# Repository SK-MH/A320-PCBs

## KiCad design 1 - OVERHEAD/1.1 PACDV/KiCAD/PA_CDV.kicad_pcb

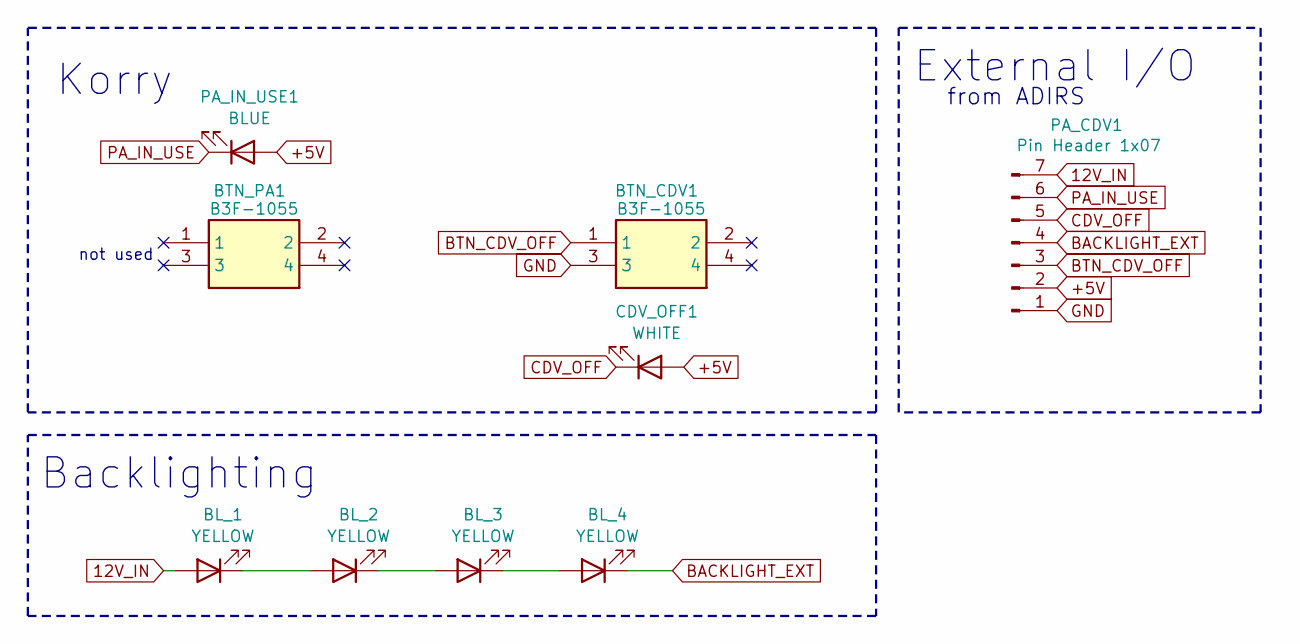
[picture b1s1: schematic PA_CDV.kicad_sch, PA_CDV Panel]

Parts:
BL_1, BL_2, BL_3, BL_4: YELLOW; LED_D3.0mm
BTN_CDV1: B3F-1055; B3F1000; Mouser Part Number 653-B3F-1055
BTN_PA1: B3F-1055; B3F1000; Mouser Part Number 653-B3F-1055
CDV_OFF1: WHITE; LED_D3.0mm
PA_CDV1: Pin Header 1x07; JST_EH_B7B-EH-A_1x07_P2.50mm_Vertical
PA_IN_USE1: BLUE; LED_D3.0mm

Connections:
12V_IN: BL_1.2 (A), PA_CDV1.7
+5V: CDV_OFF1.2 (A), PA_CDV1.2, PA_IN_USE1.2 (A)
BACKLIGHT_EXT: BL_4.1 (K), PA_CDV1.4
BTN_CDV_OFF: BTN_CDV1.1, PA_CDV1.3
CDV_OFF: CDV_OFF1.1 (K), PA_CDV1.5
GND: BTN_CDV1.3, PA_CDV1.1
unnamed: BL_1.1 (K), BL_2.2 (A)
unnamed: BL_2.1 (K), BL_3.2 (A)
unnamed: BL_3.1 (K), BL_4.2 (A)
PA_IN_USE: PA_CDV1.6, PA_IN_USE1.1 (K)

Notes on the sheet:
External I/O
from ADIRS
Backlighting
Korry
not used

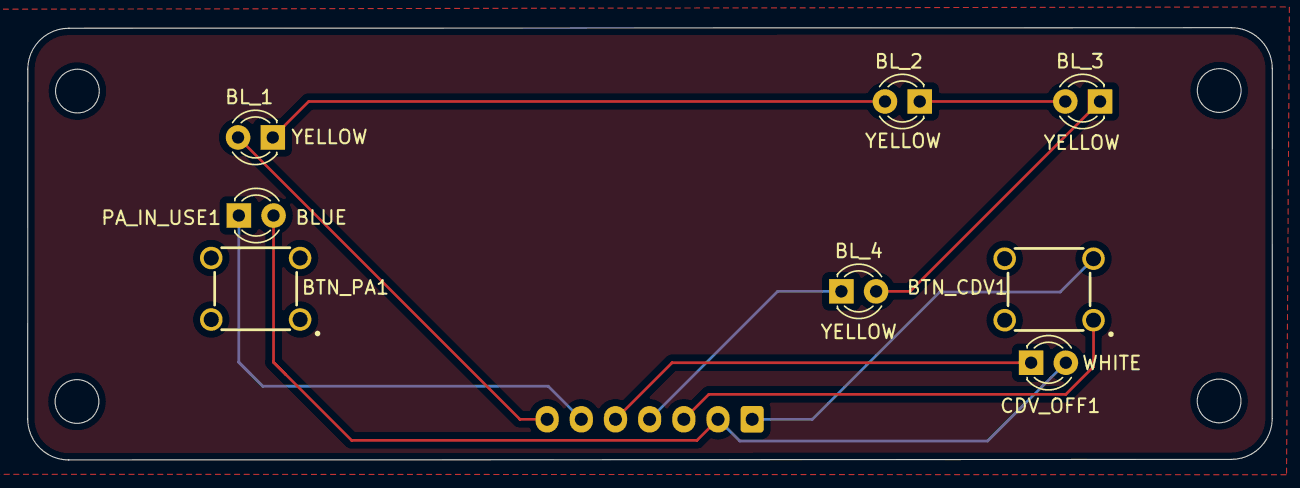
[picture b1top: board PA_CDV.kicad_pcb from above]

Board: 2 copper layers, 91.0 x 31.6 mm, 9 parts (1 on the bottom side), 10 nets.

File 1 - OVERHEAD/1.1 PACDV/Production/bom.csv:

Designator,Footprint,Quantity,Value,LCSC Part #
CDV_OFF1,LED_D3.0mm,1,WHITE,
"BL_1, BL_2, BL_3, BL_4",LED_D3.0mm,4,YELLOW,
"BTN_CDV1, BTN_PA1",B3F1000,2,B3F-1055,
PA_CDV1,JST_EH_B7B-EH-A_1x07_P2.50mm_Vertical,1,Pin Header 1x07,
PA_IN_USE1,LED_D3.0mm,1,BLUE,

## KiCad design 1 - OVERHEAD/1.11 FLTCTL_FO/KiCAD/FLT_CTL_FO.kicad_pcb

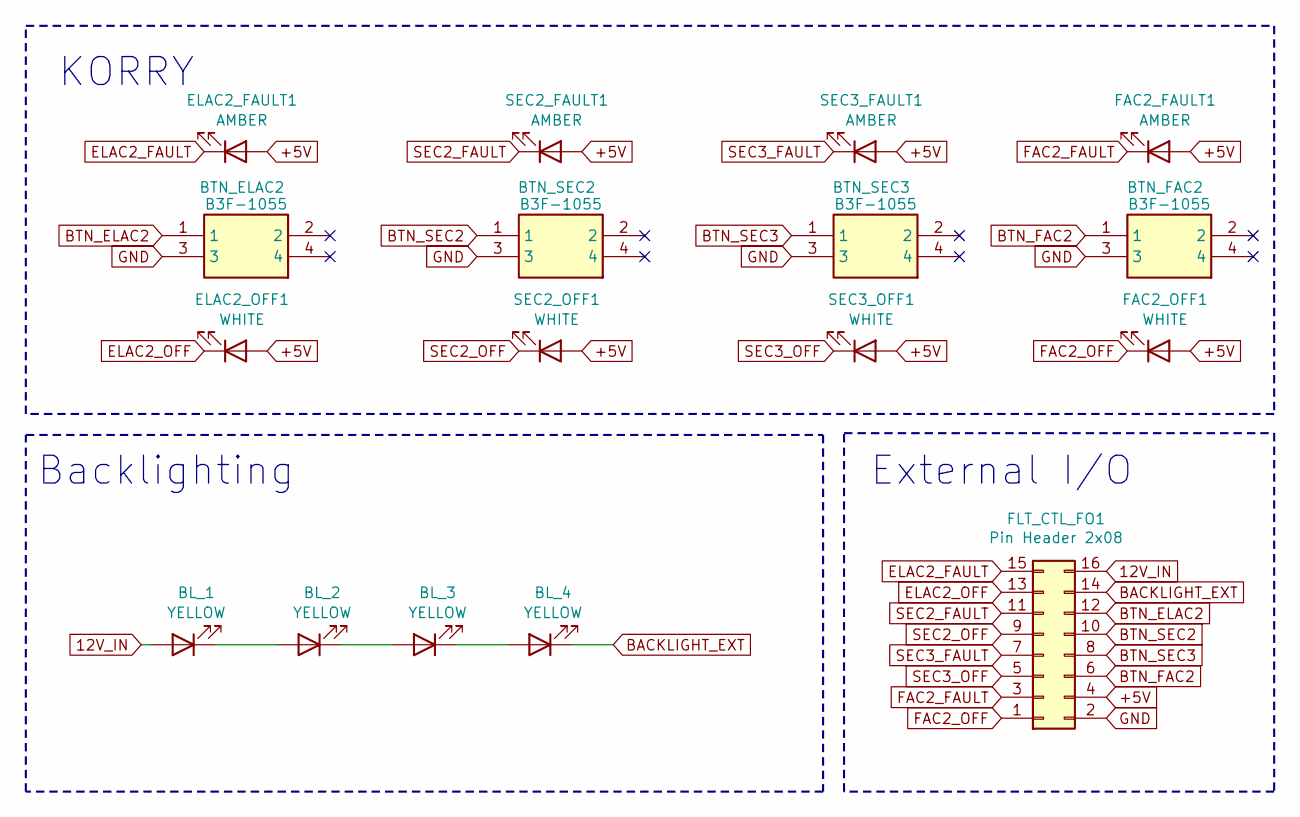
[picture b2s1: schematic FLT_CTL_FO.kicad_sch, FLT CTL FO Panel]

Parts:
BL_1, BL_2, BL_3, BL_4: YELLOW; LED_D3.0mm
BTN_ELAC2: B3F-1055; B3F1000; Mouser Part Number 653-B3F-1055
BTN_FAC2: B3F-1055; B3F1000; Mouser Part Number 653-B3F-1055
BTN_SEC2, BTN_SEC3: B3F-1055; B3F1000; Mouser Part Number 653-B3F-1055
ELAC2_FAULT1: AMBER; LED_D3.0mm
ELAC2_OFF1: WHITE; LED_D3.0mm
FAC2_FAULT1: AMBER; LED_D3.0mm
FAC2_OFF1: WHITE; LED_D3.0mm
FLT_CTL_FO1: Pin Header 2x08; IDC-Header_2x08_P2.54mm_Vertical
SEC2_FAULT1, SEC3_FAULT1: AMBER; LED_D3.0mm
SEC2_OFF1, SEC3_OFF1: WHITE; LED_D3.0mm

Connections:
12V_IN: BL_1.2 (A), FLT_CTL_FO1.16
+5V: ELAC2_FAULT1.2 (A), ELAC2_OFF1.2 (A), FAC2_FAULT1.2 (A), FAC2_OFF1.2 (A), FLT_CTL_FO1.4, SEC2_FAULT1.2 (A), SEC2_OFF1.2 (A), SEC3_FAULT1.2 (A), SEC3_OFF1.2 (A)
BACKLIGHT_EXT: BL_4.1 (K), FLT_CTL_FO1.14
BTN_ELAC2: BTN_ELAC2.1, FLT_CTL_FO1.12
BTN_FAC2: BTN_FAC2.1, FLT_CTL_FO1.6
BTN_SEC2: BTN_SEC2.1, FLT_CTL_FO1.10
BTN_SEC3: BTN_SEC3.1, FLT_CTL_FO1.8
ELAC2_FAULT: ELAC2_FAULT1.1 (K), FLT_CTL_FO1.15
ELAC2_OFF: ELAC2_OFF1.1 (K), FLT_CTL_FO1.13
FAC2_FAULT: FAC2_FAULT1.1 (K), FLT_CTL_FO1.3
FAC2_OFF: FAC2_OFF1.1 (K), FLT_CTL_FO1.1
GND: BTN_ELAC2.3, BTN_FAC2.3, BTN_SEC2.3, BTN_SEC3.3, FLT_CTL_FO1.2
unnamed: BL_1.1 (K), BL_2.2 (A)
unnamed: BL_2.1 (K), BL_3.2 (A)
unnamed: BL_3.1 (K), BL_4.2 (A)
SEC2_FAULT: FLT_CTL_FO1.11, SEC2_FAULT1.1 (K)
SEC2_OFF: FLT_CTL_FO1.9, SEC2_OFF1.1 (K)
SEC3_FAULT: FLT_CTL_FO1.7, SEC3_FAULT1.1 (K)
SEC3_OFF: FLT_CTL_FO1.5, SEC3_OFF1.1 (K)

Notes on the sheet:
Backlighting
External I/O
KORRY

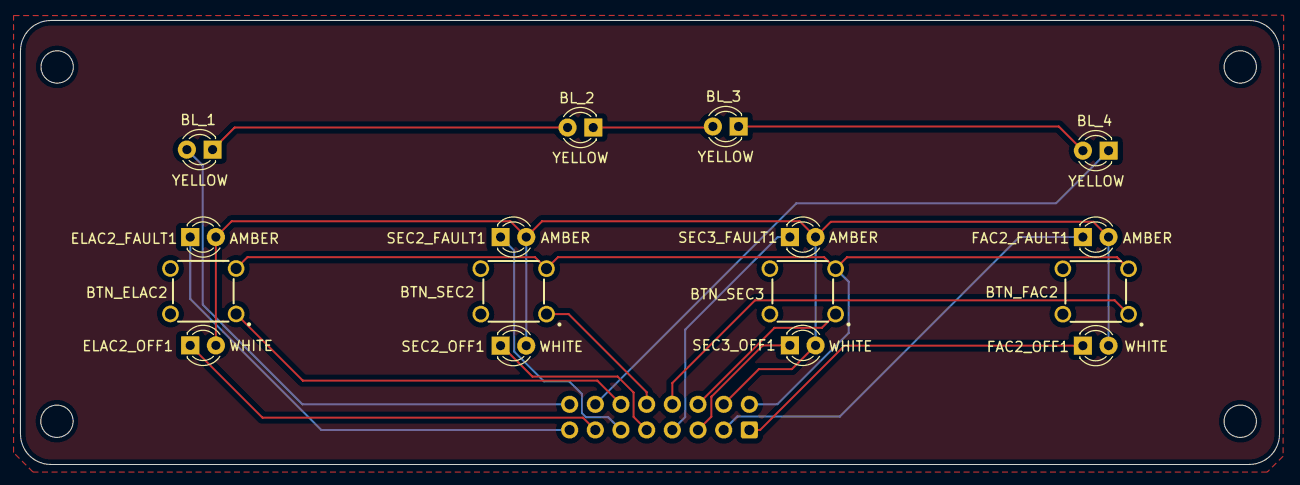
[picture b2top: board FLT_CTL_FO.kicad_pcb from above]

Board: 2 copper layers, 124.6 x 43.9 mm, 17 parts (1 on the bottom side), 19 nets.

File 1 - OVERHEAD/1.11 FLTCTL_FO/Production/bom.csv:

Designator,Footprint,Quantity,Value,LCSC Part #
"BL_1, BL_2, BL_3, BL_4",LED_D3.0mm,4,YELLOW,
"BTN_ELAC2, BTN_FAC2, BTN_SEC2, BTN_SEC3",B3F1000,4,B3F-1055,
"ELAC2_FAULT1, FAC2_FAULT1, SEC2_FAULT1, SEC3_FAULT1",LED_D3.0mm,4,AMBER,
"ELAC2_OFF1, FAC2_OFF1, SEC2_OFF1, SEC3_OFF1",LED_D3.0mm,4,WHITE,
FLT_CTL_FO1,IDC-Header_2x08_P2.54mm_Vertical,1,Pin Header 2x08,

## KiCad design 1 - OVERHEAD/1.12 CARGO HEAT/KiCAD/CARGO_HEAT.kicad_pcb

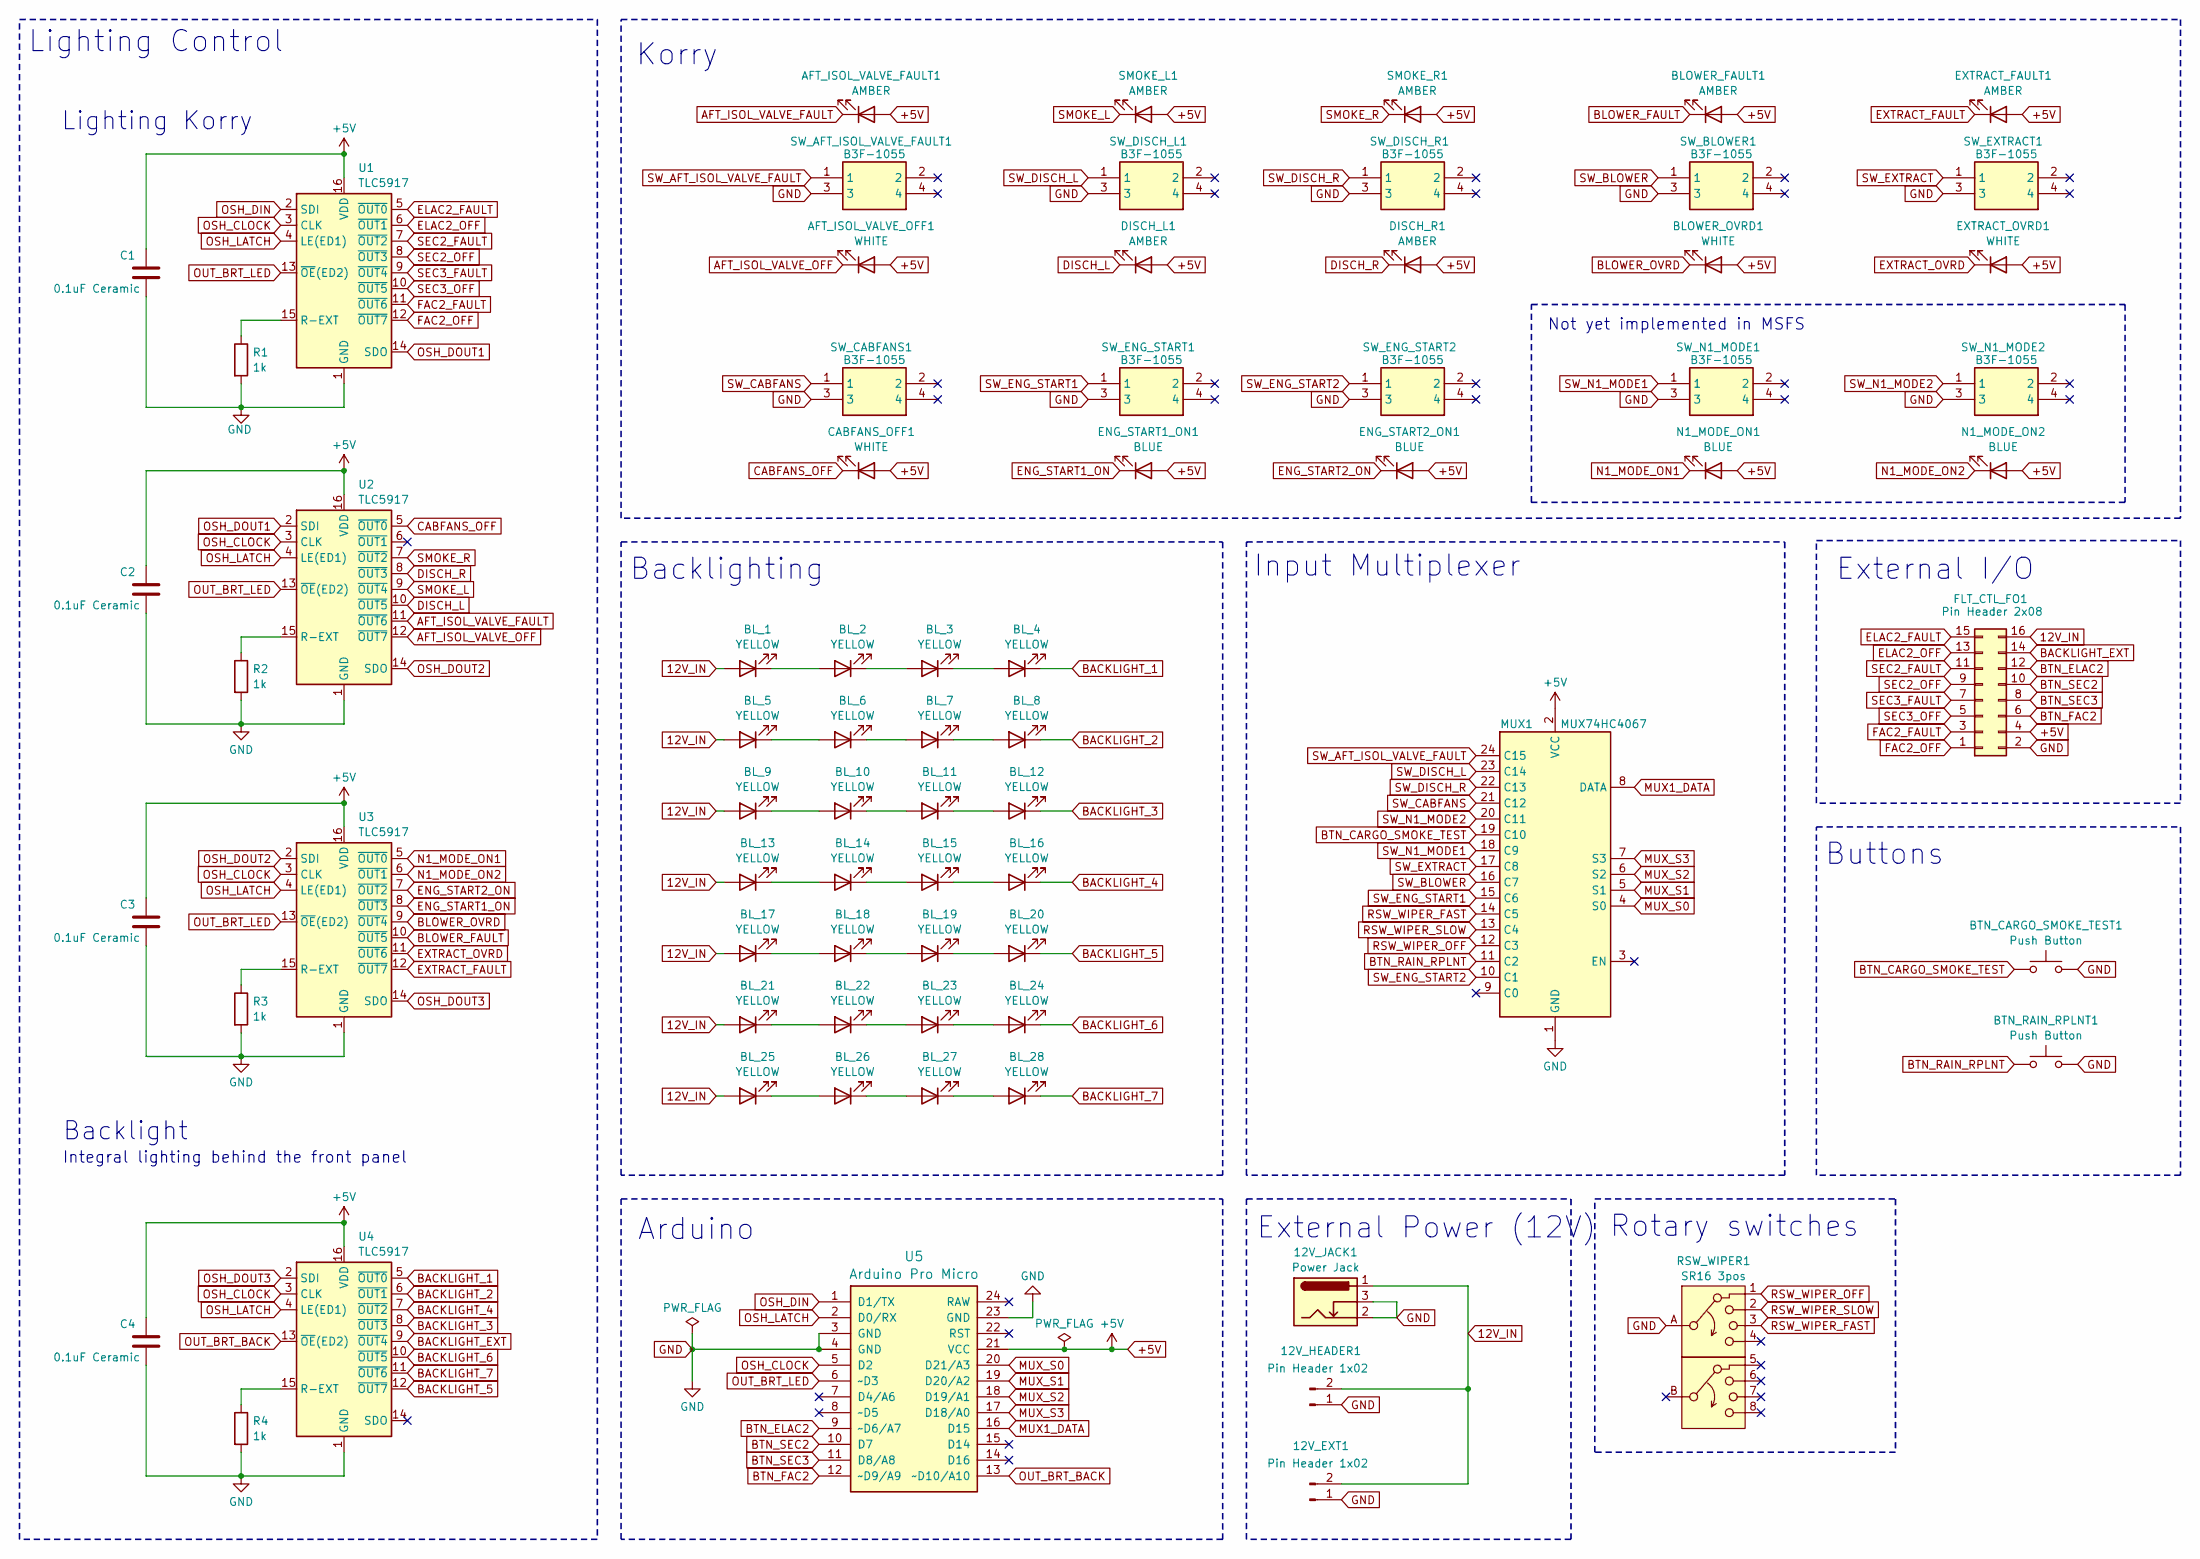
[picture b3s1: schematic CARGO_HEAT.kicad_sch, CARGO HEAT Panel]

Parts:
12V_EXT1, 12V_HEADER1: Pin Header 1x02; JST_EH_B2B-EH-A_1x02_P2.50mm_Vertical
12V_JACK1: Power Jack; BarrelJack_Horizontal
AFT_ISOL_VALVE_FAULT1: AMBER; LED_D3.0mm
AFT_ISOL_VALVE_OFF1: WHITE; LED_D3.0mm
BLOWER_FAULT1: AMBER; LED_D3.0mm
BLOWER_OVRD1: WHITE; LED_D3.0mm
BL_1, BL_2, BL_3, BL_4, BL_5, BL_6, BL_7, BL_8, BL_9, BL_10, BL_11, BL_12, BL_13, BL_14, BL_15, BL_16, BL_17, BL_18, BL_19, BL_20, BL_21, BL_22, BL_23, BL_24, BL_25, BL_26, BL_27, BL_28: YELLOW; LED_D3.0mm
BTN_CARGO_SMOKE_TEST1: Push Button; SW-Push
BTN_RAIN_RPLNT1: Push Button; SW-Push
C1, C2, C3, C4: 0.1uF Ceramic; C_Disc_D3.0mm_W1.6mm_P2.50mm
CABFANS_OFF1: WHITE; LED_D3.0mm
DISCH_L1: AMBER; LED_D3.0mm
DISCH_R1: AMBER; LED_D3.0mm
ENG_START1_ON1, ENG_START2_ON1: BLUE; LED_D3.0mm
EXTRACT_FAULT1: AMBER; LED_D3.0mm
EXTRACT_OVRD1: WHITE; LED_D3.0mm
FLT_CTL_FO1: Pin Header 2x08; IDC-Header_2x08_P2.54mm_Vertical
MUX1: MUX74HC4067
N1_MODE_ON1, N1_MODE_ON2: BLUE; LED_D3.0mm
R1, R2, R3, R4: 1k; R_Axial_DIN0204_L3.6mm_D1.6mm_P7.62mm_Horizontal
RSW_WIPER1: SR16 3pos; SR16-AB
SMOKE_L1: AMBER; LED_D3.0mm
SMOKE_R1: AMBER; LED_D3.0mm
SW_AFT_ISOL_VALVE_FAULT1: B3F-1055; B3F1000; Mouser Part Number 653-B3F-1055
SW_BLOWER1: B3F-1055; B3F1000; Mouser Part Number 653-B3F-1055
SW_CABFANS1: B3F-1055; B3F1000; Mouser Part Number 653-B3F-1055
SW_DISCH_L1: B3F-1055; B3F1000; Mouser Part Number 653-B3F-1055
SW_DISCH_R1: B3F-1055; B3F1000; Mouser Part Number 653-B3F-1055
SW_ENG_START1, SW_ENG_START2: B3F-1055; B3F1000; Mouser Part Number 653-B3F-1055
SW_EXTRACT1: B3F-1055; B3F1000; Mouser Part Number 653-B3F-1055
SW_N1_MODE1, SW_N1_MODE2: B3F-1055; B3F1000; Mouser Part Number 653-B3F-1055
U1, U2, U3, U4: TLC5917; DIP-16_W7.62mm
U5: Arduino Pro Micro; Sparkfun_Pro_Micro

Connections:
12V_IN: 12V_EXT1.2, 12V_HEADER1.2, 12V_JACK1.1, BL_1.2 (A), BL_5.2 (A), BL_9.2 (A), BL_13.2 (A), BL_17.2 (A), BL_21.2 (A), BL_25.2 (A), FLT_CTL_FO1.16
+5V: AFT_ISOL_VALVE_FAULT1.2 (A), AFT_ISOL_VALVE_OFF1.2 (A), BLOWER_FAULT1.2 (A), BLOWER_OVRD1.2 (A), C1.1, C2.1, C3.1, C4.1, CABFANS_OFF1.2 (A), DISCH_L1.2 (A), DISCH_R1.2 (A), ENG_START1_ON1.2 (A), ENG_START2_ON1.2 (A), EXTRACT_FAULT1.2 (A), EXTRACT_OVRD1.2 (A), FLT_CTL_FO1.4, MUX1.2 (VCC), N1_MODE_ON1.2 (A), N1_MODE_ON2.2 (A), SMOKE_L1.2 (A), SMOKE_R1.2 (A), U1.16 (VDD), U2.16 (VDD), U3.16 (VDD), U4.16 (VDD), U5.21 (VCC)
AFT_ISOL_VALVE_FAULT: AFT_ISOL_VALVE_FAULT1.1 (K), U2.11 (~OUT6)
AFT_ISOL_VALVE_OFF: AFT_ISOL_VALVE_OFF1.1 (K), U2.12 (~OUT7)
BACKLIGHT_1: BL_4.1 (K), U4.5 (~OUT0)
BACKLIGHT_2: BL_8.1 (K), U4.6 (~OUT1)
BACKLIGHT_3: BL_12.1 (K), U4.8 (~OUT3)
BACKLIGHT_4: BL_16.1 (K), U4.7 (~OUT2)
BACKLIGHT_5: BL_20.1 (K), U4.12 (~OUT7)
BACKLIGHT_6: BL_24.1 (K), U4.10 (~OUT5)
BACKLIGHT_7: BL_28.1 (K), U4.11 (~OUT6)
BACKLIGHT_EXT: FLT_CTL_FO1.14, U4.9 (~OUT4)
BLOWER_FAULT: BLOWER_FAULT1.1 (K), U3.10 (~OUT5)
BLOWER_OVRD: BLOWER_OVRD1.1 (K), U3.9 (~OUT4)
BTN_CARGO_SMOKE_TEST: BTN_CARGO_SMOKE_TEST1.1, MUX1.19 (C10)
BTN_ELAC2: FLT_CTL_FO1.12, U5.9 (~D6/A7)
BTN_FAC2: FLT_CTL_FO1.6, U5.12 (~D9/A9)
BTN_RAIN_RPLNT: BTN_RAIN_RPLNT1.1, MUX1.11 (C2)
BTN_SEC2: FLT_CTL_FO1.10, U5.10 (D7)
BTN_SEC3: FLT_CTL_FO1.8, U5.11 (D8/A8)
CABFANS_OFF: CABFANS_OFF1.1 (K), U2.5 (~OUT0)
DISCH_L: DISCH_L1.1 (K), U2.10 (~OUT5)
DISCH_R: DISCH_R1.1 (K), U2.8 (~OUT3)
ELAC2_FAULT: FLT_CTL_FO1.15, U1.5 (~OUT0)
ELAC2_OFF: FLT_CTL_FO1.13, U1.6 (~OUT1)
ENG_START1_ON: ENG_START1_ON1.1 (K), U3.8 (~OUT3)
ENG_START2_ON: ENG_START2_ON1.1 (K), U3.7 (~OUT2)
EXTRACT_FAULT: EXTRACT_FAULT1.1 (K), U3.12 (~OUT7)
EXTRACT_OVRD: EXTRACT_OVRD1.1 (K), U3.11 (~OUT6)
FAC2_FAULT: FLT_CTL_FO1.3, U1.11 (~OUT6)
FAC2_OFF: FLT_CTL_FO1.1, U1.12 (~OUT7)
GND: 12V_EXT1.1, 12V_HEADER1.1, 12V_JACK1.2, 12V_JACK1.3, BTN_CARGO_SMOKE_TEST1.2, BTN_RAIN_RPLNT1.2, C1.2, C2.2, C3.2, C4.2, FLT_CTL_FO1.2, MUX1.1 (GND), R1.2, R2.2, R3.2, R4.2, RSW_WIPER1.A, SW_AFT_ISOL_VALVE_FAULT1.3, SW_BLOWER1.3, SW_CABFANS1.3, SW_DISCH_L1.3, SW_DISCH_R1.3, SW_ENG_START1.3, SW_ENG_START2.3, SW_EXTRACT1.3, SW_N1_MODE1.3, SW_N1_MODE2.3, U1.1 (GND), U2.1 (GND), U3.1 (GND), U4.1 (GND), U5.3 (GND), U5.4 (GND), U5.23 (GND)
MUX1_DATA: MUX1.8 (DATA), U5.16 (D15)
MUX_S0: MUX1.4 (S0), U5.20 (D21/A3)
MUX_S1: MUX1.5 (S1), U5.19 (D20/A2)
MUX_S2: MUX1.6 (S2), U5.18 (D19/A1)
MUX_S3: MUX1.7 (S3), U5.17 (D18/A0)
N1_MODE_ON1: N1_MODE_ON1.1 (K), U3.5 (~OUT0)
N1_MODE_ON2: N1_MODE_ON2.1 (K), U3.6 (~OUT1)
unnamed: BL_1.1 (K), BL_2.2 (A)
unnamed: BL_2.1 (K), BL_3.2 (A)
unnamed: BL_3.1 (K), BL_4.2 (A)
unnamed: BL_5.1 (K), BL_6.2 (A)
unnamed: BL_6.1 (K), BL_7.2 (A)
unnamed: BL_7.1 (K), BL_8.2 (A)
unnamed: BL_9.1 (K), BL_10.2 (A)
unnamed: BL_10.1 (K), BL_11.2 (A)
unnamed: BL_11.1 (K), BL_12.2 (A)
unnamed: BL_13.1 (K), BL_14.2 (A)
unnamed: BL_14.1 (K), BL_15.2 (A)
unnamed: BL_15.1 (K), BL_16.2 (A)
unnamed: BL_17.1 (K), BL_18.2 (A)
unnamed: BL_18.1 (K), BL_19.2 (A)
unnamed: BL_19.1 (K), BL_20.2 (A)
unnamed: BL_21.1 (K), BL_22.2 (A)
unnamed: BL_22.1 (K), BL_23.2 (A)
unnamed: BL_23.1 (K), BL_24.2 (A)
unnamed: BL_25.1 (K), BL_26.2 (A)
unnamed: BL_26.1 (K), BL_27.2 (A)
unnamed: BL_27.1 (K), BL_28.2 (A)
unnamed: R1.1, U1.15 (R-EXT)
unnamed: R2.1, U2.15 (R-EXT)
unnamed: R3.1, U3.15 (R-EXT)
unnamed: R4.1, U4.15 (R-EXT)
OSH_CLOCK: U1.3 (CLK), U2.3 (CLK), U3.3 (CLK), U4.3 (CLK), U5.5 (D2)
OSH_DIN: U1.2 (SDI), U5.1 (D1/TX)
OSH_DOUT1: U1.14 (SDO), U2.2 (SDI)
OSH_DOUT2: U2.14 (SDO), U3.2 (SDI)
OSH_DOUT3: U3.14 (SDO), U4.2 (SDI)
OSH_LATCH: U1.4 (LE(ED1)), U2.4 (LE(ED1)), U3.4 (LE(ED1)), U4.4 (LE(ED1)), U5.2 (D0/RX)
OUT_BRT_BACK: U4.13 (~OE(ED2)), U5.13 (~D10/A10)
OUT_BRT_LED: U1.13 (~OE(ED2)), U2.13 (~OE(ED2)), U3.13 (~OE(ED2)), U5.6 (~D3)
RSW_WIPER_FAST: MUX1.14 (C5), RSW_WIPER1.3
RSW_WIPER_OFF: MUX1.12 (C3), RSW_WIPER1.1
RSW_WIPER_SLOW: MUX1.13 (C4), RSW_WIPER1.2
SEC2_FAULT: FLT_CTL_FO1.11, U1.7 (~OUT2)
SEC2_OFF: FLT_CTL_FO1.9, U1.8 (~OUT3)
SEC3_FAULT: FLT_CTL_FO1.7, U1.9 (~OUT4)
SEC3_OFF: FLT_CTL_FO1.5, U1.10 (~OUT5)
SMOKE_L: SMOKE_L1.1 (K), U2.9 (~OUT4)
SMOKE_R: SMOKE_R1.1 (K), U2.7 (~OUT2)
SW_AFT_ISOL_VALVE_FAULT: MUX1.24 (C15), SW_AFT_ISOL_VALVE_FAULT1.1
SW_BLOWER: MUX1.16 (C7), SW_BLOWER1.1
SW_CABFANS: MUX1.21 (C12), SW_CABFANS1.1
SW_DISCH_L: MUX1.23 (C14), SW_DISCH_L1.1
SW_DISCH_R: MUX1.22 (C13), SW_DISCH_R1.1
SW_ENG_START1: MUX1.15 (C6), SW_ENG_START1.1
SW_ENG_START2: MUX1.10 (C1), SW_ENG_START2.1
SW_EXTRACT: MUX1.17 (C8), SW_EXTRACT1.1
SW_N1_MODE1: MUX1.18 (C9), SW_N1_MODE1.1
SW_N1_MODE2: MUX1.20 (C11), SW_N1_MODE2.1

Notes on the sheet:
Backlighting
Buttons
Arduino
Not yet implemented in MSFS
Korry
Input Multiplexer
External I/O
External Power (12V)
Lighting Korry
Lighting Control
Integral lighting behind the front panel
Backlight
Rotary switches

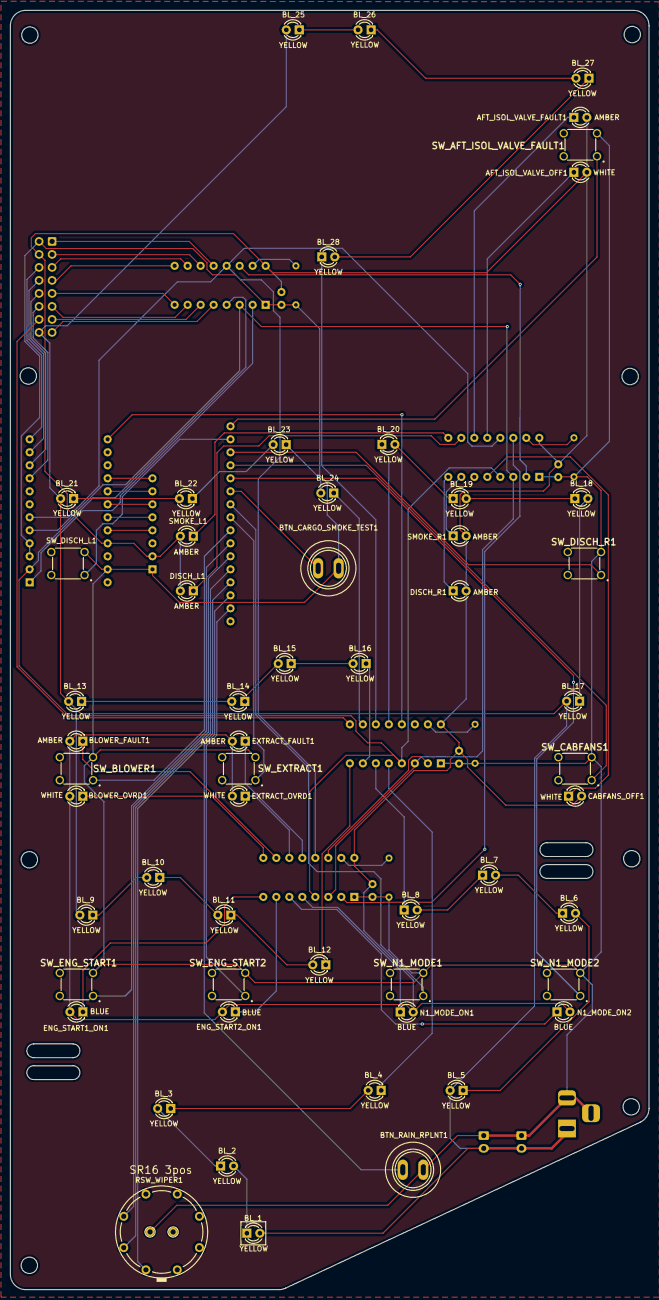
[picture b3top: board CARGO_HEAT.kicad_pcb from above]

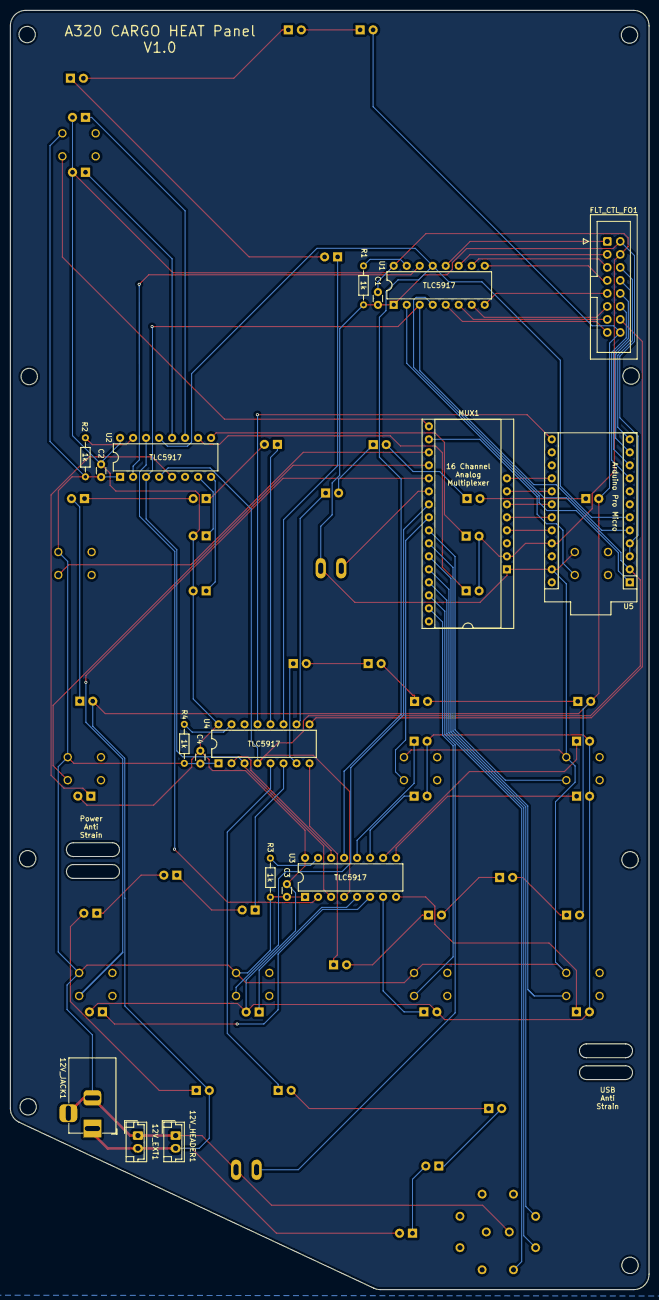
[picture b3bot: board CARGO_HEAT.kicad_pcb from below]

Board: 2 copper layers, 124.8 x 249.9 mm, 74 parts (18 on the bottom side), 91 nets.

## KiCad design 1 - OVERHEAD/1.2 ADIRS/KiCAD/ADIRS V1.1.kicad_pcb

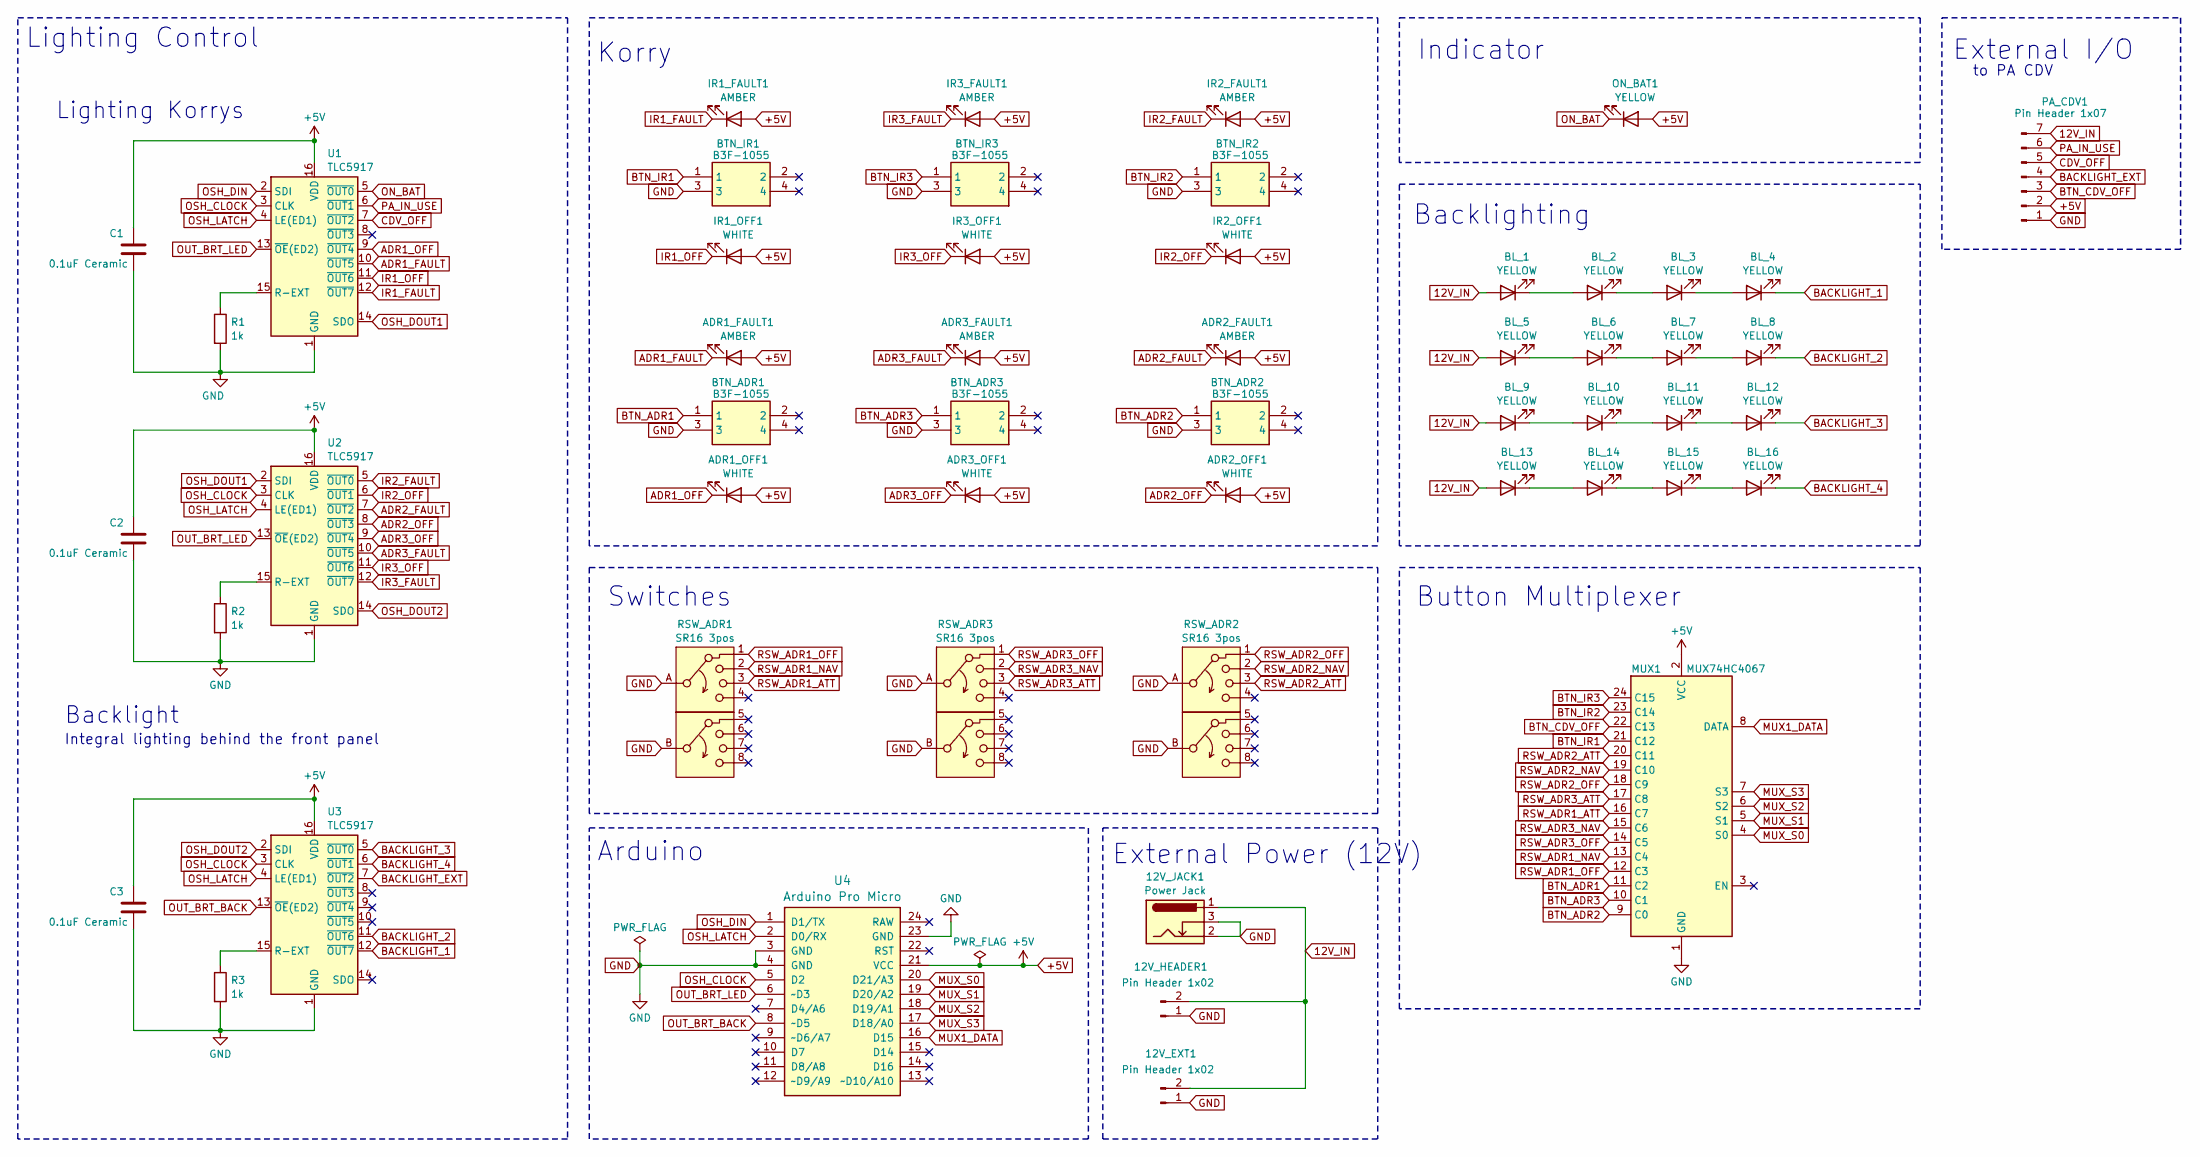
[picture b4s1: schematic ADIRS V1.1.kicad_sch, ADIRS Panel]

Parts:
12V_EXT1, 12V_HEADER1: Pin Header 1x02; JST_EH_B2B-EH-A_1x02_P2.50mm_Vertical
12V_JACK1: Power Jack; BarrelJack_Horizontal
ADR1_FAULT1, ADR2_FAULT1, ADR3_FAULT1: AMBER; LED_D3.0mm
ADR1_OFF1, ADR2_OFF1, ADR3_OFF1: WHITE; LED_D3.0mm
BL_1, BL_2, BL_3, BL_4, BL_5, BL_6, BL_7, BL_8, BL_9, BL_10, BL_11, BL_12, BL_13, BL_14, BL_15, BL_16: YELLOW; LED_D3.0mm
BTN_ADR1, BTN_ADR2, BTN_ADR3: B3F-1055; B3F1000; Mouser Part Number 653-B3F-1055
BTN_IR1, BTN_IR2, BTN_IR3: B3F-1055; B3F1000; Mouser Part Number 653-B3F-1055
C1, C2, C3: 0.1uF Ceramic; C_Disc_D3.0mm_W1.6mm_P2.50mm
IR1_FAULT1, IR2_FAULT1, IR3_FAULT1: AMBER; LED_D3.0mm
IR1_OFF1, IR2_OFF1, IR3_OFF1: WHITE; LED_D3.0mm
MUX1: MUX74HC4067
ON_BAT1: YELLOW; LED_D3.0mm
PA_CDV1: Pin Header 1x07; JST_EH_B7B-EH-A_1x07_P2.50mm_Vertical
R1, R2, R3: 1k; R_Axial_DIN0204_L3.6mm_D1.6mm_P7.62mm_Horizontal
RSW_ADR1, RSW_ADR2, RSW_ADR3: SR16 3pos; SR16-AB
U1, U2, U3: TLC5917; DIP-16_W7.62mm
U4: Arduino Pro Micro; Sparkfun_Pro_Micro

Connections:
12V_IN: 12V_EXT1.2, 12V_HEADER1.2, 12V_JACK1.1, BL_1.2 (A), BL_5.2 (A), BL_9.2 (A), BL_13.2 (A), PA_CDV1.7
+5V: ADR1_FAULT1.2 (A), ADR1_OFF1.2 (A), ADR2_FAULT1.2 (A), ADR2_OFF1.2 (A), ADR3_FAULT1.2 (A), ADR3_OFF1.2 (A), C1.1, C2.1, C3.1, IR1_FAULT1.2 (A), IR1_OFF1.2 (A), IR2_FAULT1.2 (A), IR2_OFF1.2 (A), IR3_FAULT1.2 (A), IR3_OFF1.2 (A), MUX1.2 (VCC), ON_BAT1.2 (A), PA_CDV1.2, U1.16 (VDD), U2.16 (VDD), U3.16 (VDD), U4.21 (VCC)
ADR1_FAULT: ADR1_FAULT1.1 (K), U1.10 (~OUT5)
ADR1_OFF: ADR1_OFF1.1 (K), U1.9 (~OUT4)
ADR2_FAULT: ADR2_FAULT1.1 (K), U2.7 (~OUT2)
ADR2_OFF: ADR2_OFF1.1 (K), U2.8 (~OUT3)
ADR3_FAULT: ADR3_FAULT1.1 (K), U2.10 (~OUT5)
ADR3_OFF: ADR3_OFF1.1 (K), U2.9 (~OUT4)
BACKLIGHT_1: BL_4.1 (K), U3.12 (~OUT7)
BACKLIGHT_2: BL_8.1 (K), U3.11 (~OUT6)
BACKLIGHT_3: BL_12.1 (K), U3.5 (~OUT0)
BACKLIGHT_4: BL_16.1 (K), U3.6 (~OUT1)
BACKLIGHT_EXT: PA_CDV1.4, U3.7 (~OUT2)
BTN_ADR1: BTN_ADR1.1, MUX1.11 (C2)
BTN_ADR2: BTN_ADR2.1, MUX1.9 (C0)
BTN_ADR3: BTN_ADR3.1, MUX1.10 (C1)
BTN_CDV_OFF: MUX1.22 (C13), PA_CDV1.3
BTN_IR1: BTN_IR1.1, MUX1.21 (C12)
BTN_IR2: BTN_IR2.1, MUX1.23 (C14)
BTN_IR3: BTN_IR3.1, MUX1.24 (C15)
CDV_OFF: PA_CDV1.5, U1.7 (~OUT2)
GND: 12V_EXT1.1, 12V_HEADER1.1, 12V_JACK1.2, 12V_JACK1.3, BTN_ADR1.3, BTN_ADR2.3, BTN_ADR3.3, BTN_IR1.3, BTN_IR2.3, BTN_IR3.3, C1.2, C2.2, C3.2, MUX1.1 (GND), PA_CDV1.1, R1.2, R2.2, R3.2, RSW_ADR1.A, RSW_ADR1.B, RSW_ADR2.A, RSW_ADR2.B, RSW_ADR3.A, RSW_ADR3.B, U1.1 (GND), U2.1 (GND), U3.1 (GND), U4.3 (GND), U4.4 (GND), U4.23 (GND)
IR1_FAULT: IR1_FAULT1.1 (K), U1.12 (~OUT7)
IR1_OFF: IR1_OFF1.1 (K), U1.11 (~OUT6)
IR2_FAULT: IR2_FAULT1.1 (K), U2.5 (~OUT0)
IR2_OFF: IR2_OFF1.1 (K), U2.6 (~OUT1)
IR3_FAULT: IR3_FAULT1.1 (K), U2.12 (~OUT7)
IR3_OFF: IR3_OFF1.1 (K), U2.11 (~OUT6)
MUX1_DATA: MUX1.8 (DATA), U4.16 (D15)
MUX_S0: MUX1.4 (S0), U4.20 (D21/A3)
MUX_S1: MUX1.5 (S1), U4.19 (D20/A2)
MUX_S2: MUX1.6 (S2), U4.18 (D19/A1)
MUX_S3: MUX1.7 (S3), U4.17 (D18/A0)
unnamed: BL_1.1 (K), BL_2.2 (A)
unnamed: BL_2.1 (K), BL_3.2 (A)
unnamed: BL_3.1 (K), BL_4.2 (A)
unnamed: BL_5.1 (K), BL_6.2 (A)
unnamed: BL_6.1 (K), BL_7.2 (A)
unnamed: BL_7.1 (K), BL_8.2 (A)
unnamed: BL_9.1 (K), BL_10.2 (A)
unnamed: BL_10.1 (K), BL_11.2 (A)
unnamed: BL_11.1 (K), BL_12.2 (A)
unnamed: BL_13.1 (K), BL_14.2 (A)
unnamed: BL_14.1 (K), BL_15.2 (A)
unnamed: BL_15.1 (K), BL_16.2 (A)
unnamed: R1.1, U1.15 (R-EXT)
unnamed: R2.1, U2.15 (R-EXT)
unnamed: R3.1, U3.15 (R-EXT)
ON_BAT: ON_BAT1.1 (K), U1.5 (~OUT0)
OSH_CLOCK: U1.3 (CLK), U2.3 (CLK), U3.3 (CLK), U4.5 (D2)
OSH_DIN: U1.2 (SDI), U4.1 (D1/TX)
OSH_DOUT1: U1.14 (SDO), U2.2 (SDI)
OSH_DOUT2: U2.14 (SDO), U3.2 (SDI)
OSH_LATCH: U1.4 (LE(ED1)), U2.4 (LE(ED1)), U3.4 (LE(ED1)), U4.2 (D0/RX)
OUT_BRT_BACK: U3.13 (~OE(ED2)), U4.8 (~D5)
OUT_BRT_LED: U1.13 (~OE(ED2)), U2.13 (~OE(ED2)), U4.6 (~D3)
PA_IN_USE: PA_CDV1.6, U1.6 (~OUT1)
RSW_ADR1_ATT: MUX1.16 (C7), RSW_ADR1.3
RSW_ADR1_NAV: MUX1.13 (C4), RSW_ADR1.2
RSW_ADR1_OFF: MUX1.12 (C3), RSW_ADR1.1
RSW_ADR2_ATT: MUX1.20 (C11), RSW_ADR2.3
RSW_ADR2_NAV: MUX1.19 (C10), RSW_ADR2.2
RSW_ADR2_OFF: MUX1.18 (C9), RSW_ADR2.1
RSW_ADR3_ATT: MUX1.17 (C8), RSW_ADR3.3
RSW_ADR3_NAV: MUX1.15 (C6), RSW_ADR3.2
RSW_ADR3_OFF: MUX1.14 (C5), RSW_ADR3.1

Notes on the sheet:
Backlighting
External I/O
Arduino
Switches
Indicator
Korry
Button Multiplexer
to PA CDV
External Power (12V)
Lighting Korrys
Lighting Control
Integral lighting behind the front panel
Backlight

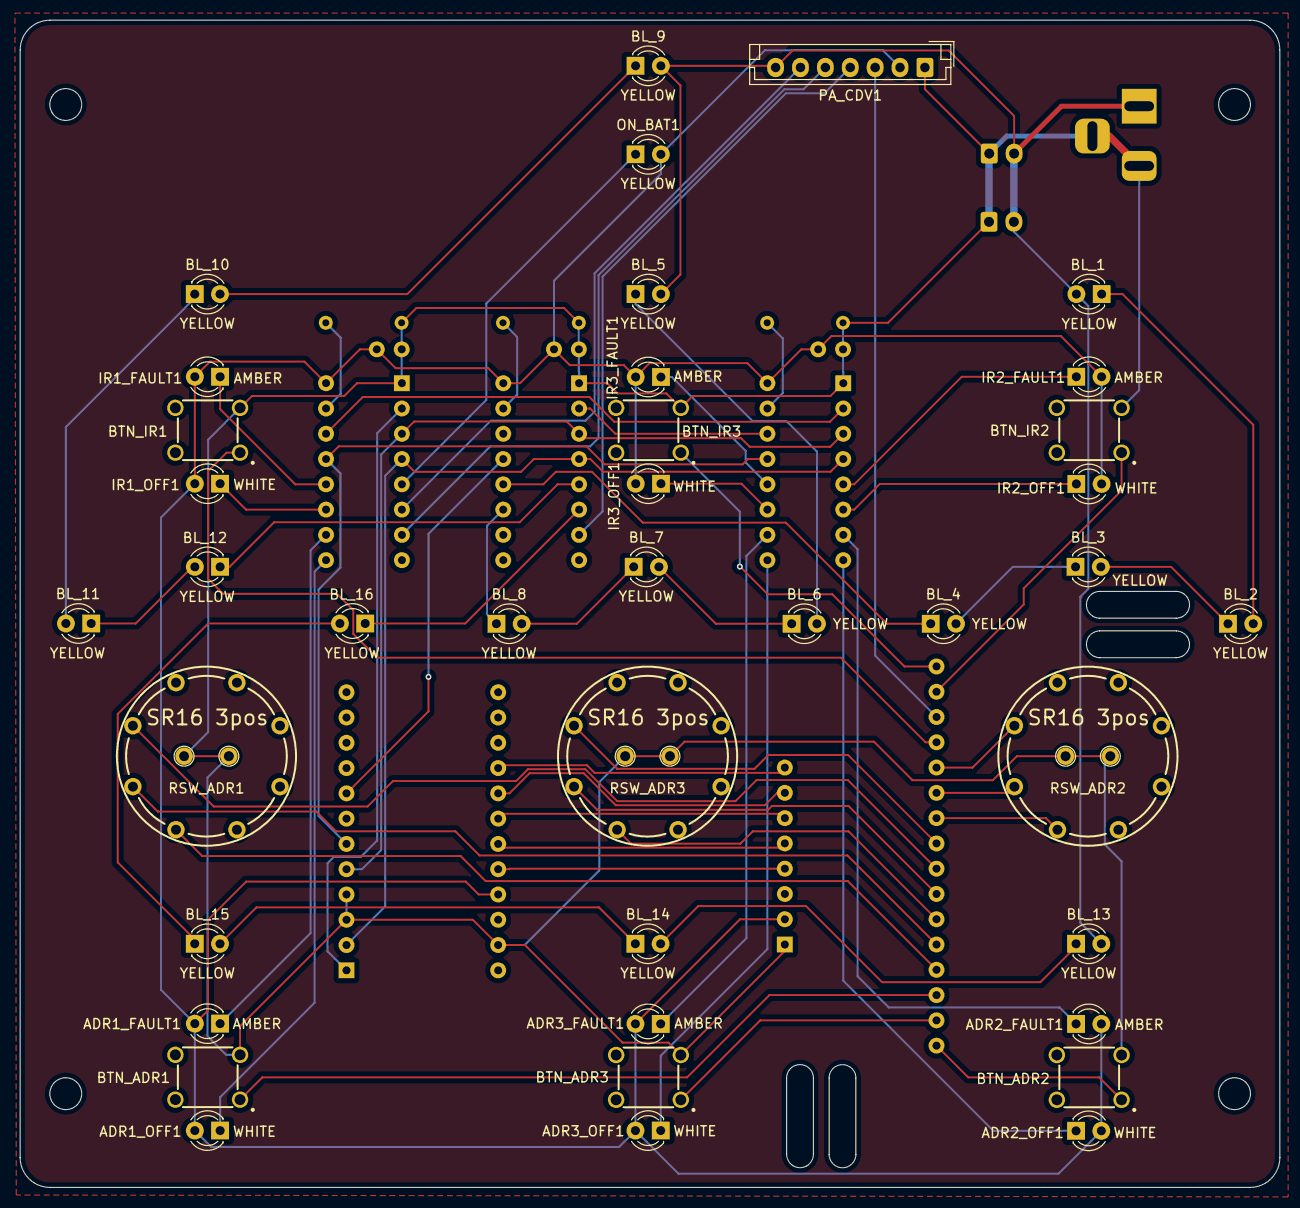
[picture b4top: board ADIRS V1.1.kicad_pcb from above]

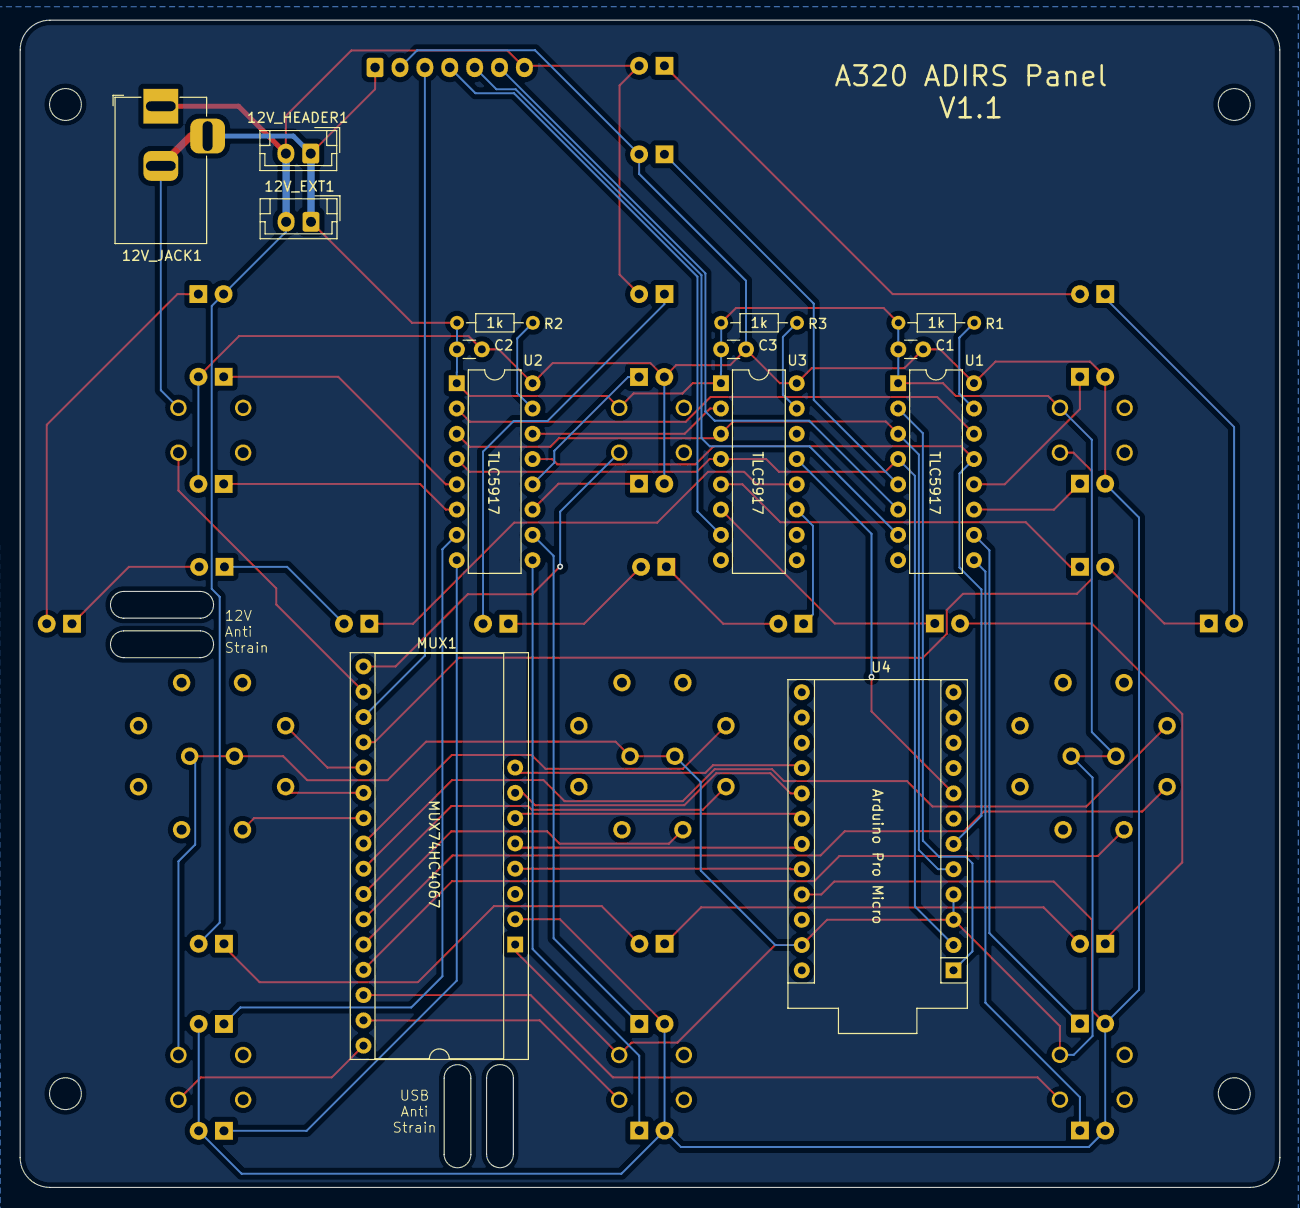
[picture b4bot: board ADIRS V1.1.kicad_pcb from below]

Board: 2 copper layers, 126.6 x 117.3 mm, 53 parts (14 on the bottom side), 66 nets.
